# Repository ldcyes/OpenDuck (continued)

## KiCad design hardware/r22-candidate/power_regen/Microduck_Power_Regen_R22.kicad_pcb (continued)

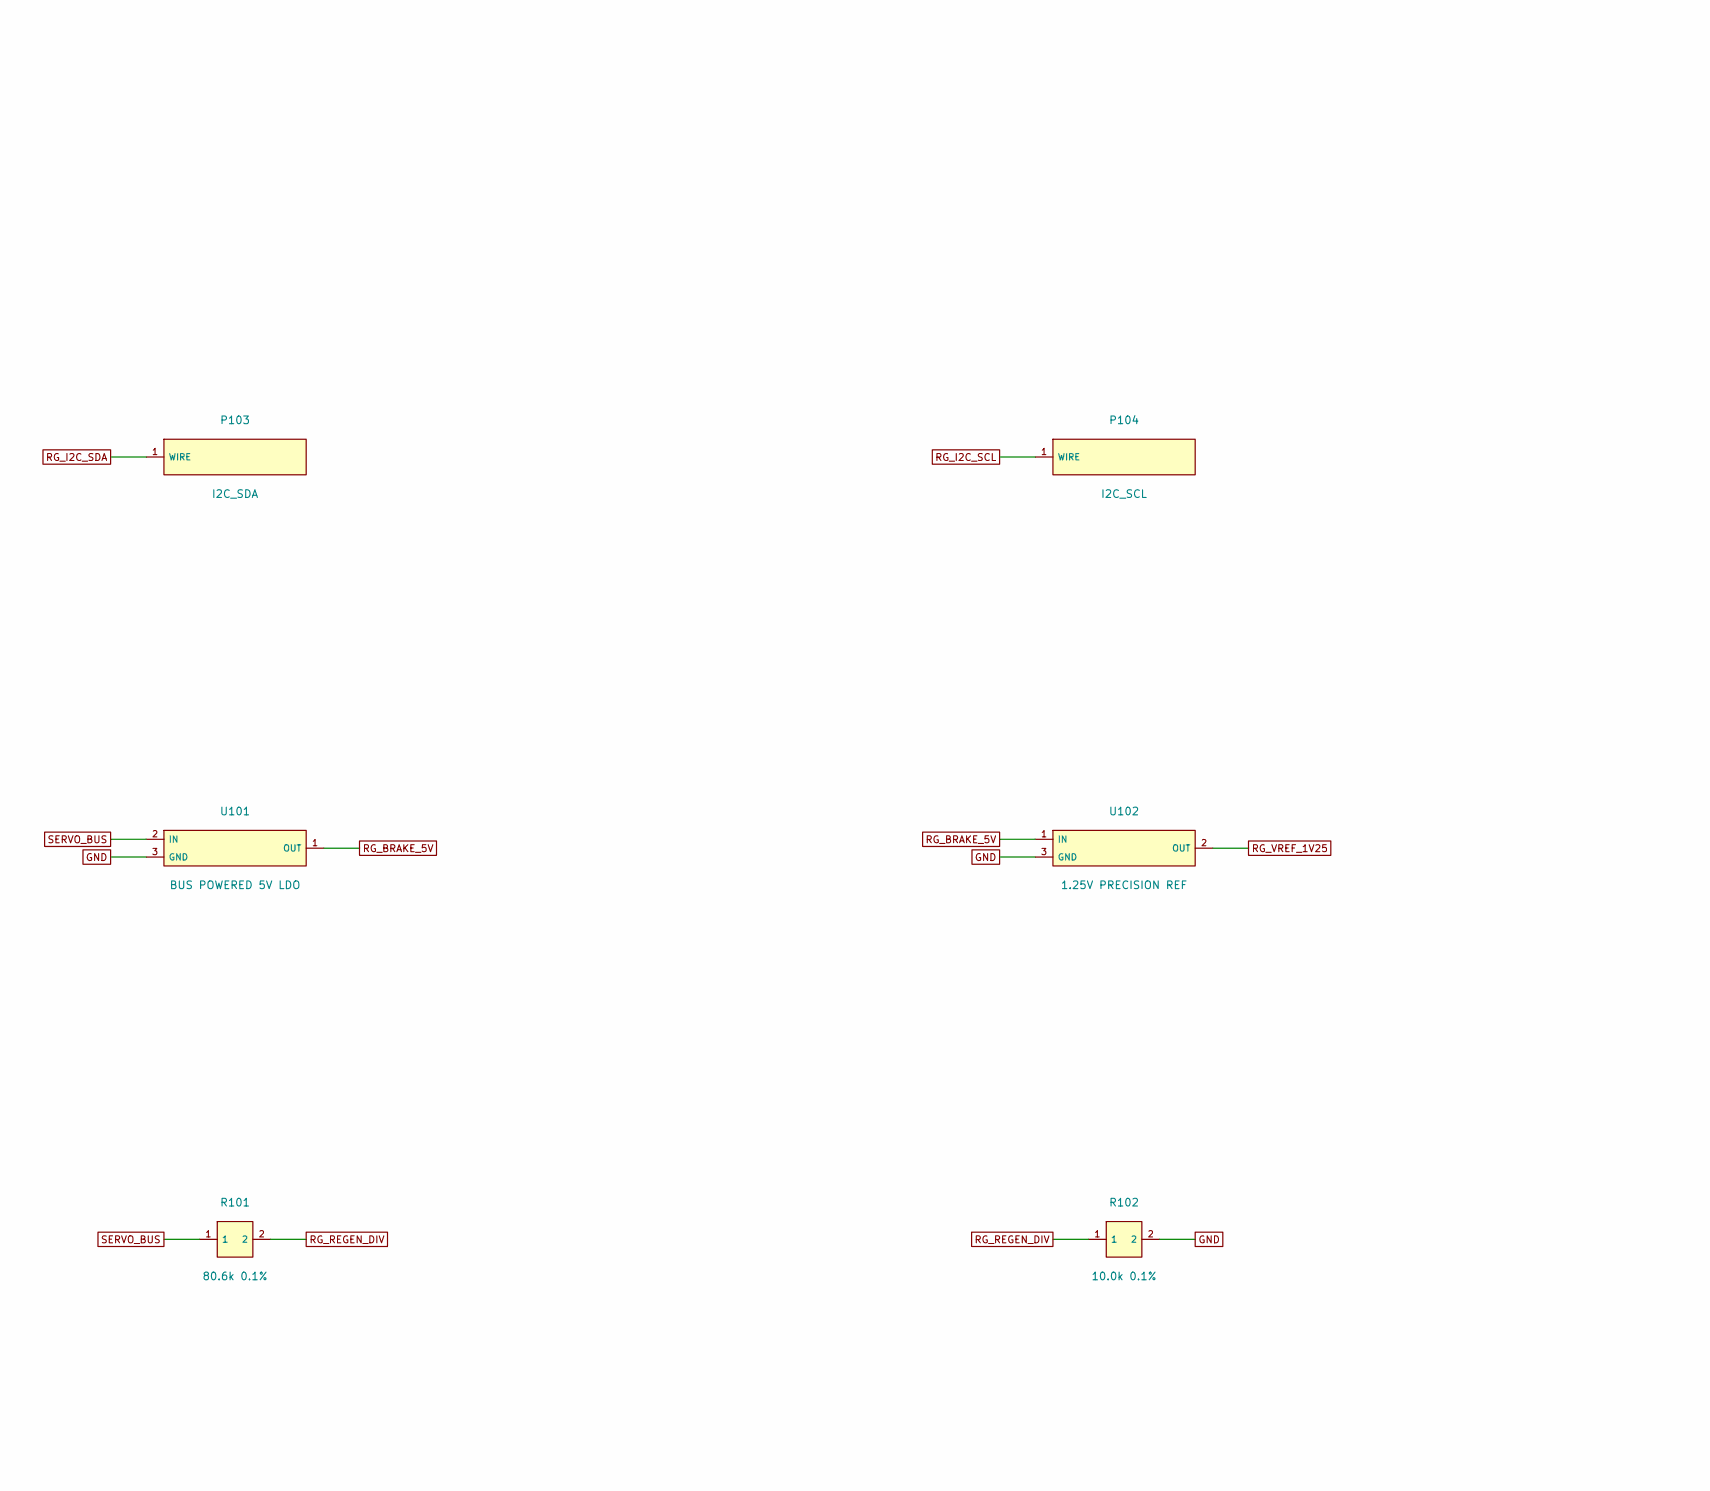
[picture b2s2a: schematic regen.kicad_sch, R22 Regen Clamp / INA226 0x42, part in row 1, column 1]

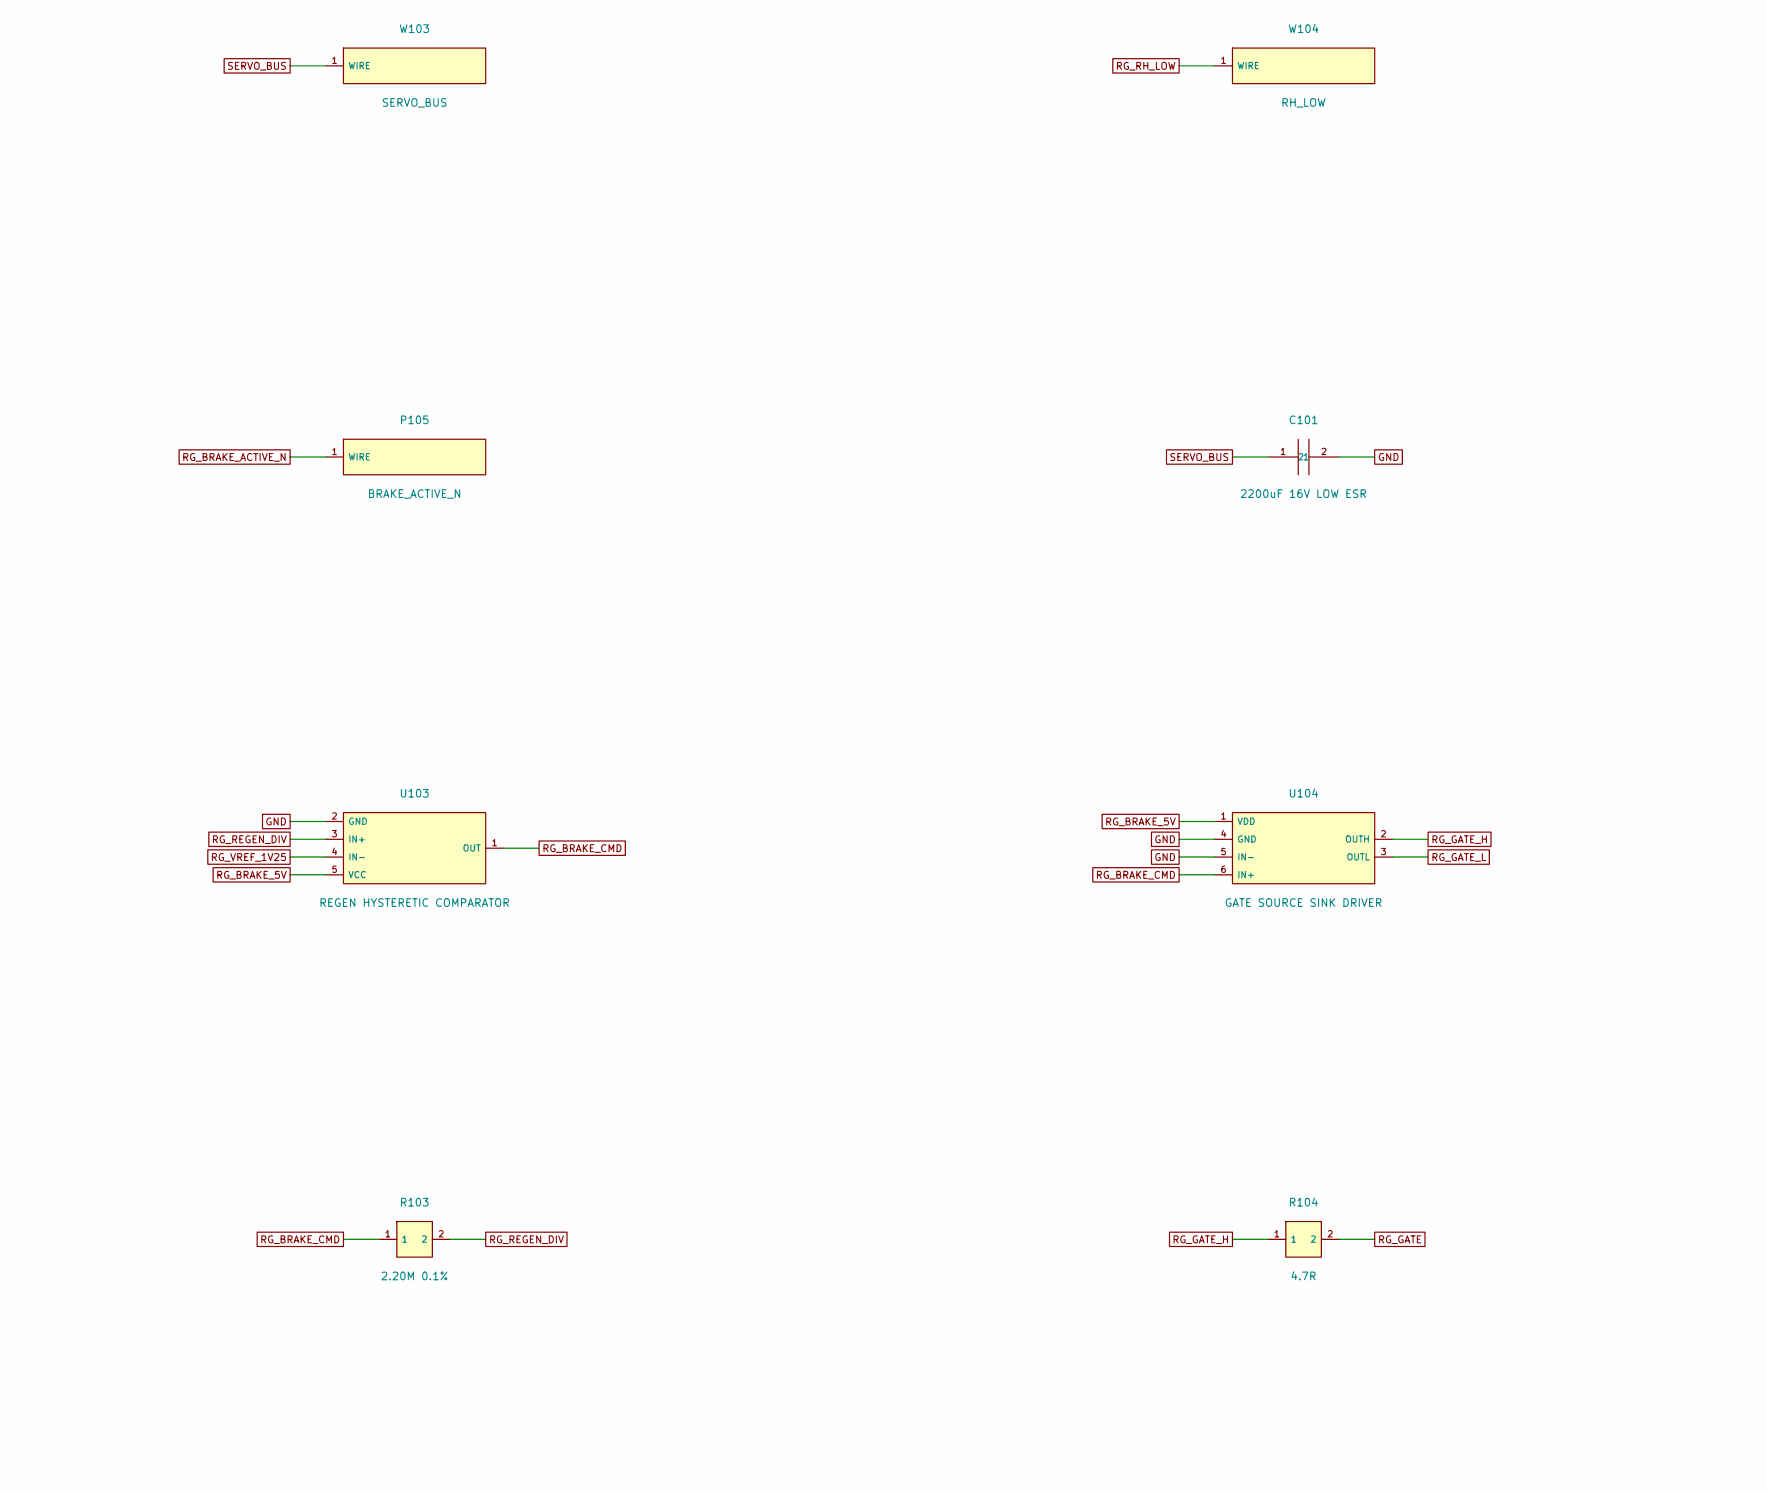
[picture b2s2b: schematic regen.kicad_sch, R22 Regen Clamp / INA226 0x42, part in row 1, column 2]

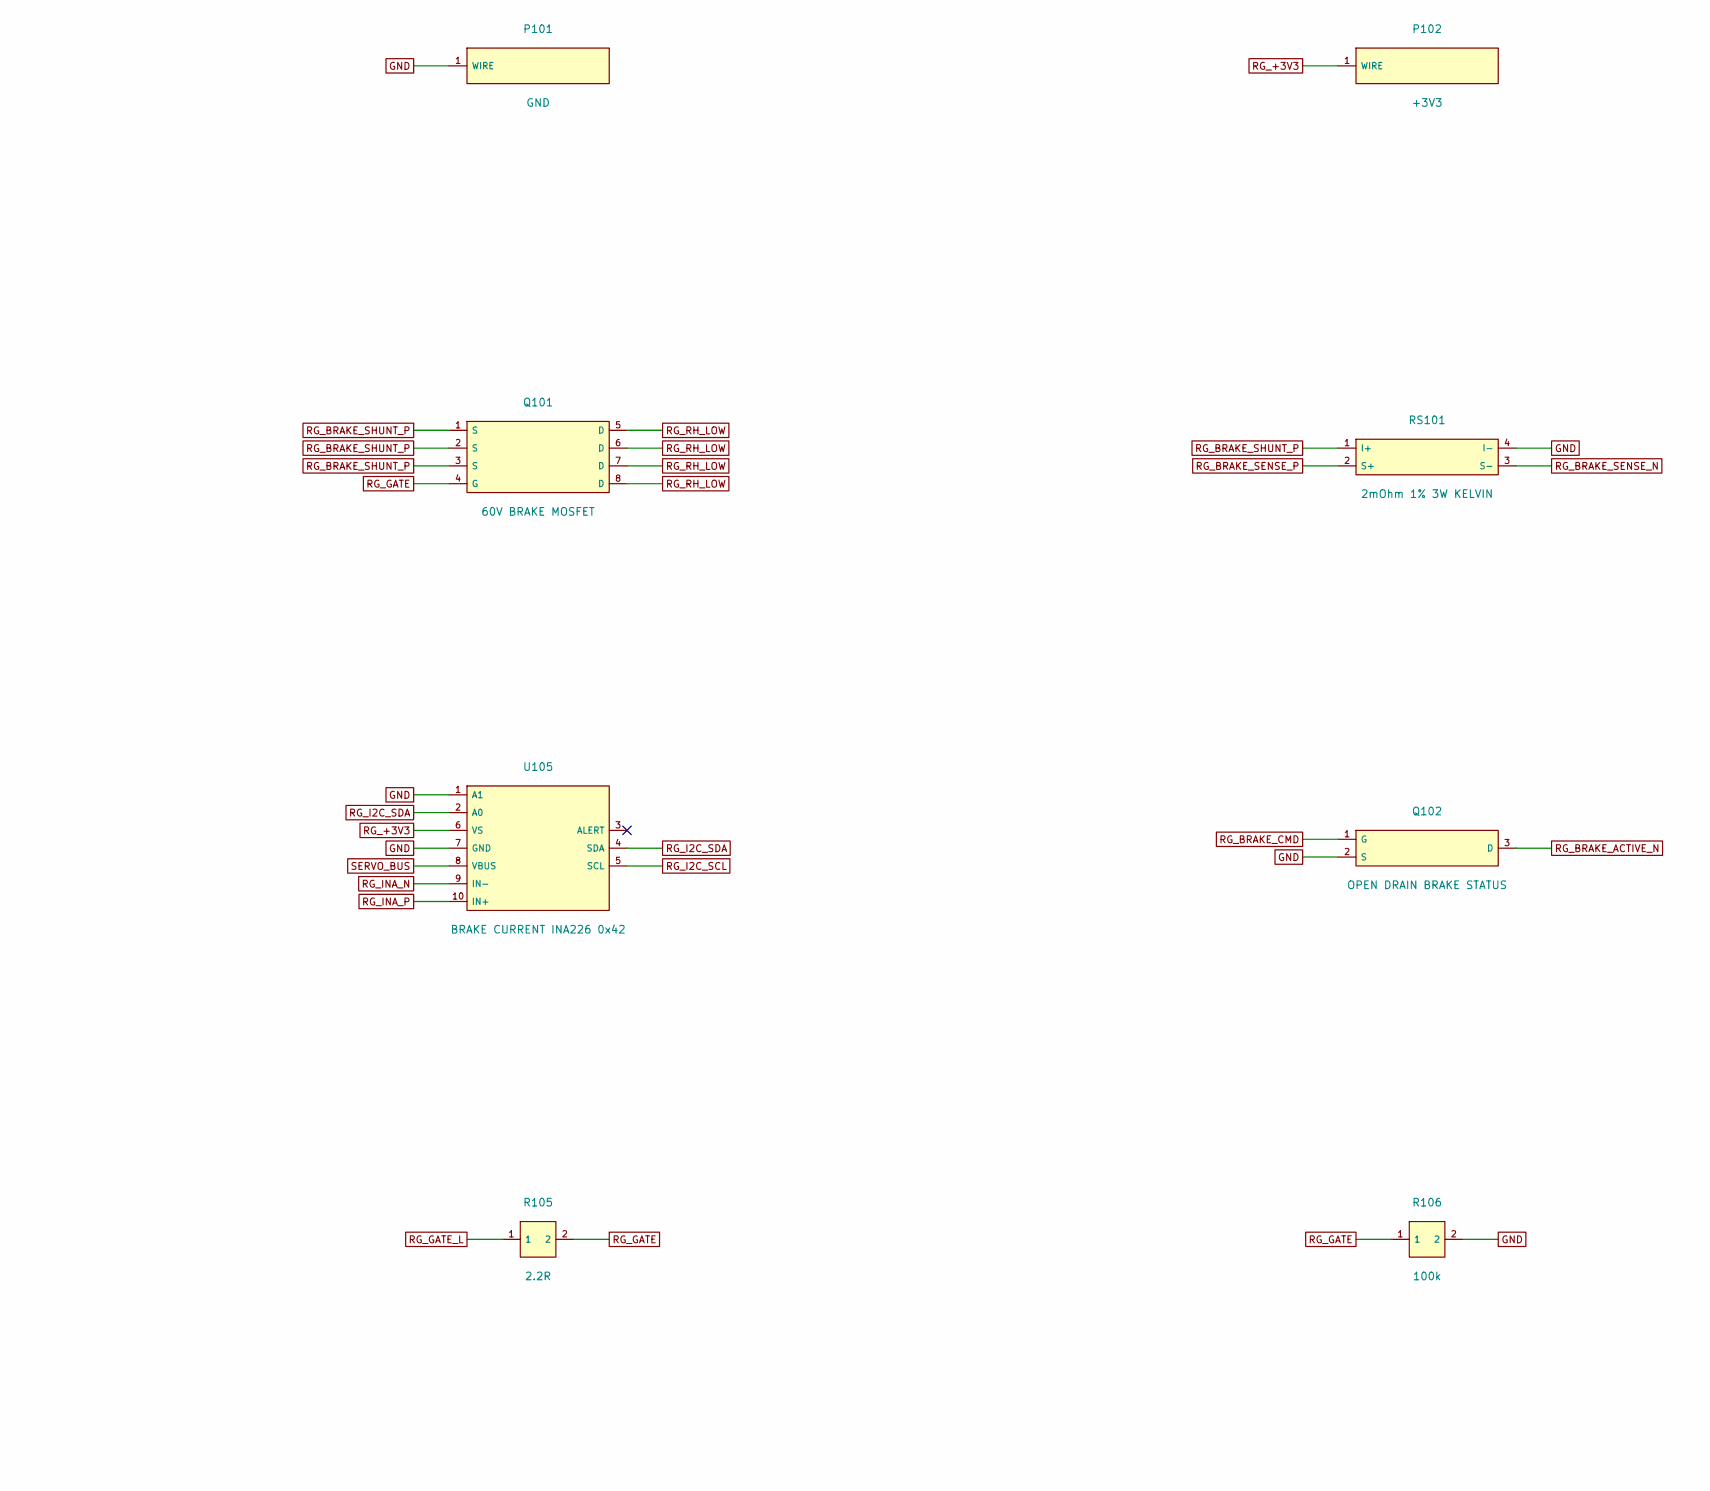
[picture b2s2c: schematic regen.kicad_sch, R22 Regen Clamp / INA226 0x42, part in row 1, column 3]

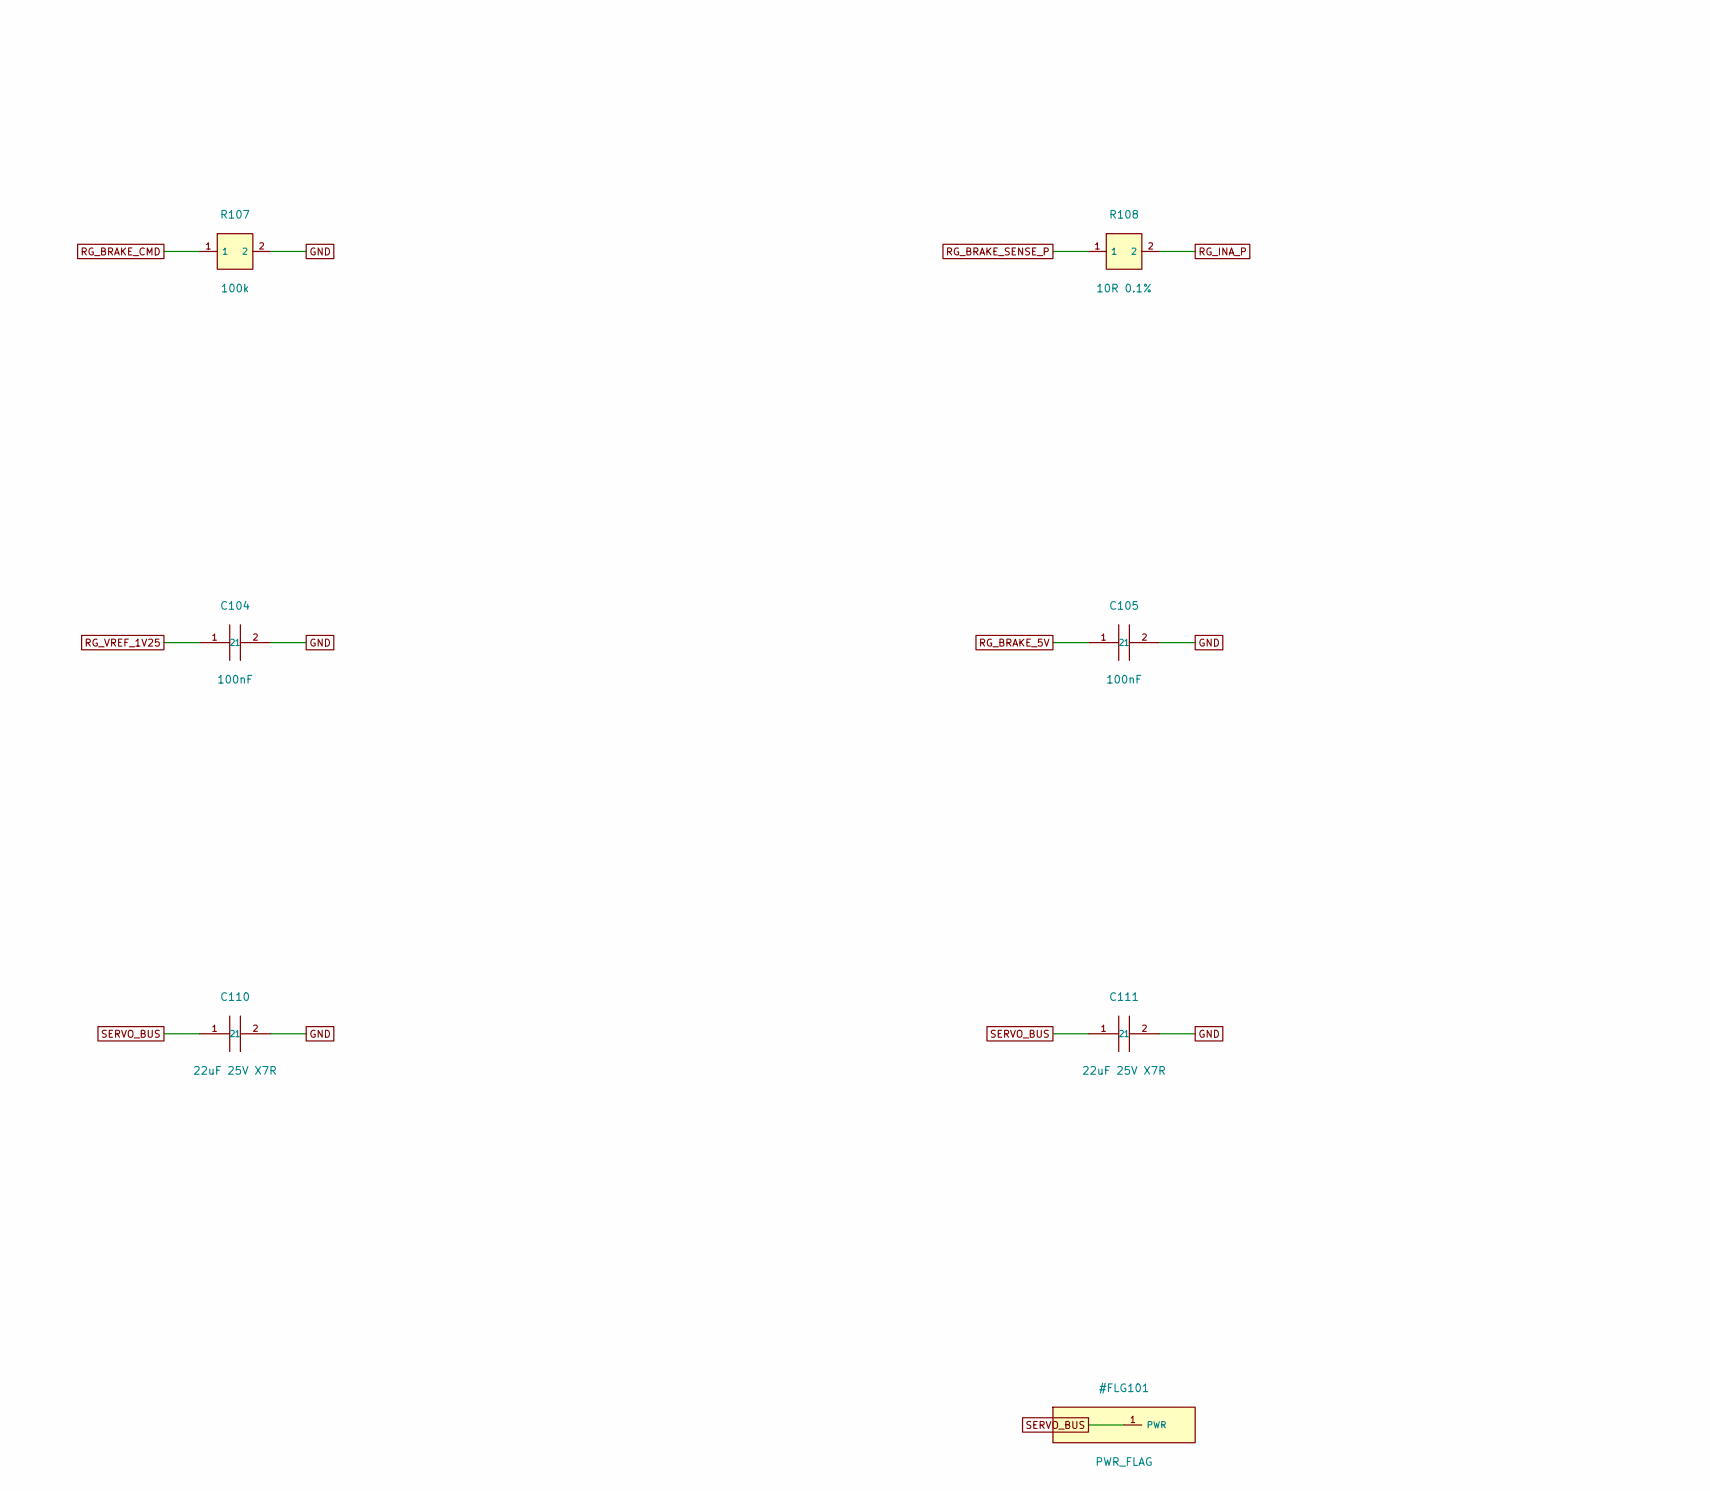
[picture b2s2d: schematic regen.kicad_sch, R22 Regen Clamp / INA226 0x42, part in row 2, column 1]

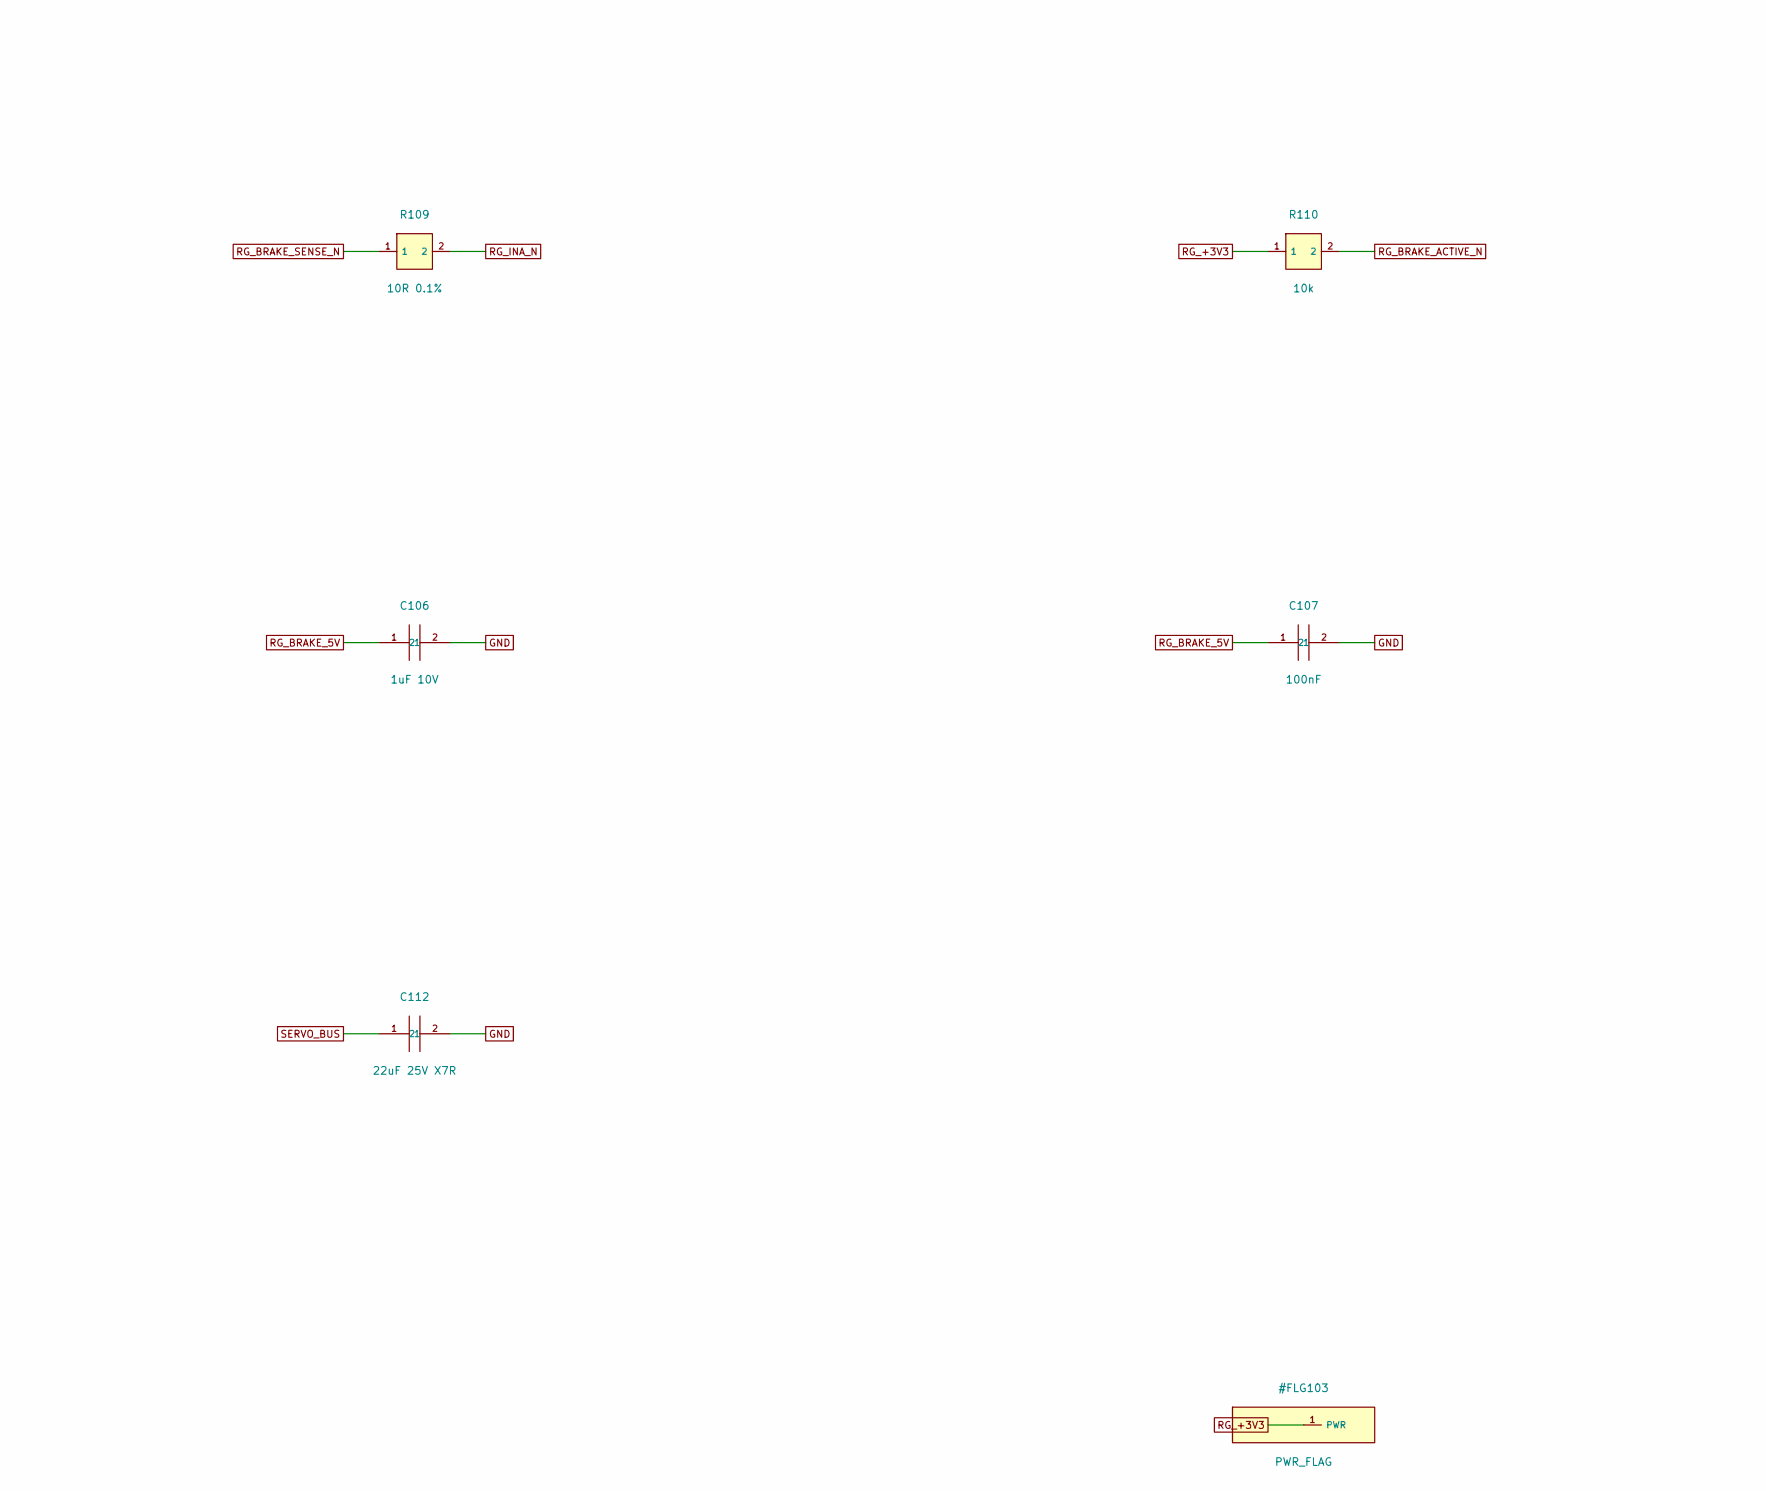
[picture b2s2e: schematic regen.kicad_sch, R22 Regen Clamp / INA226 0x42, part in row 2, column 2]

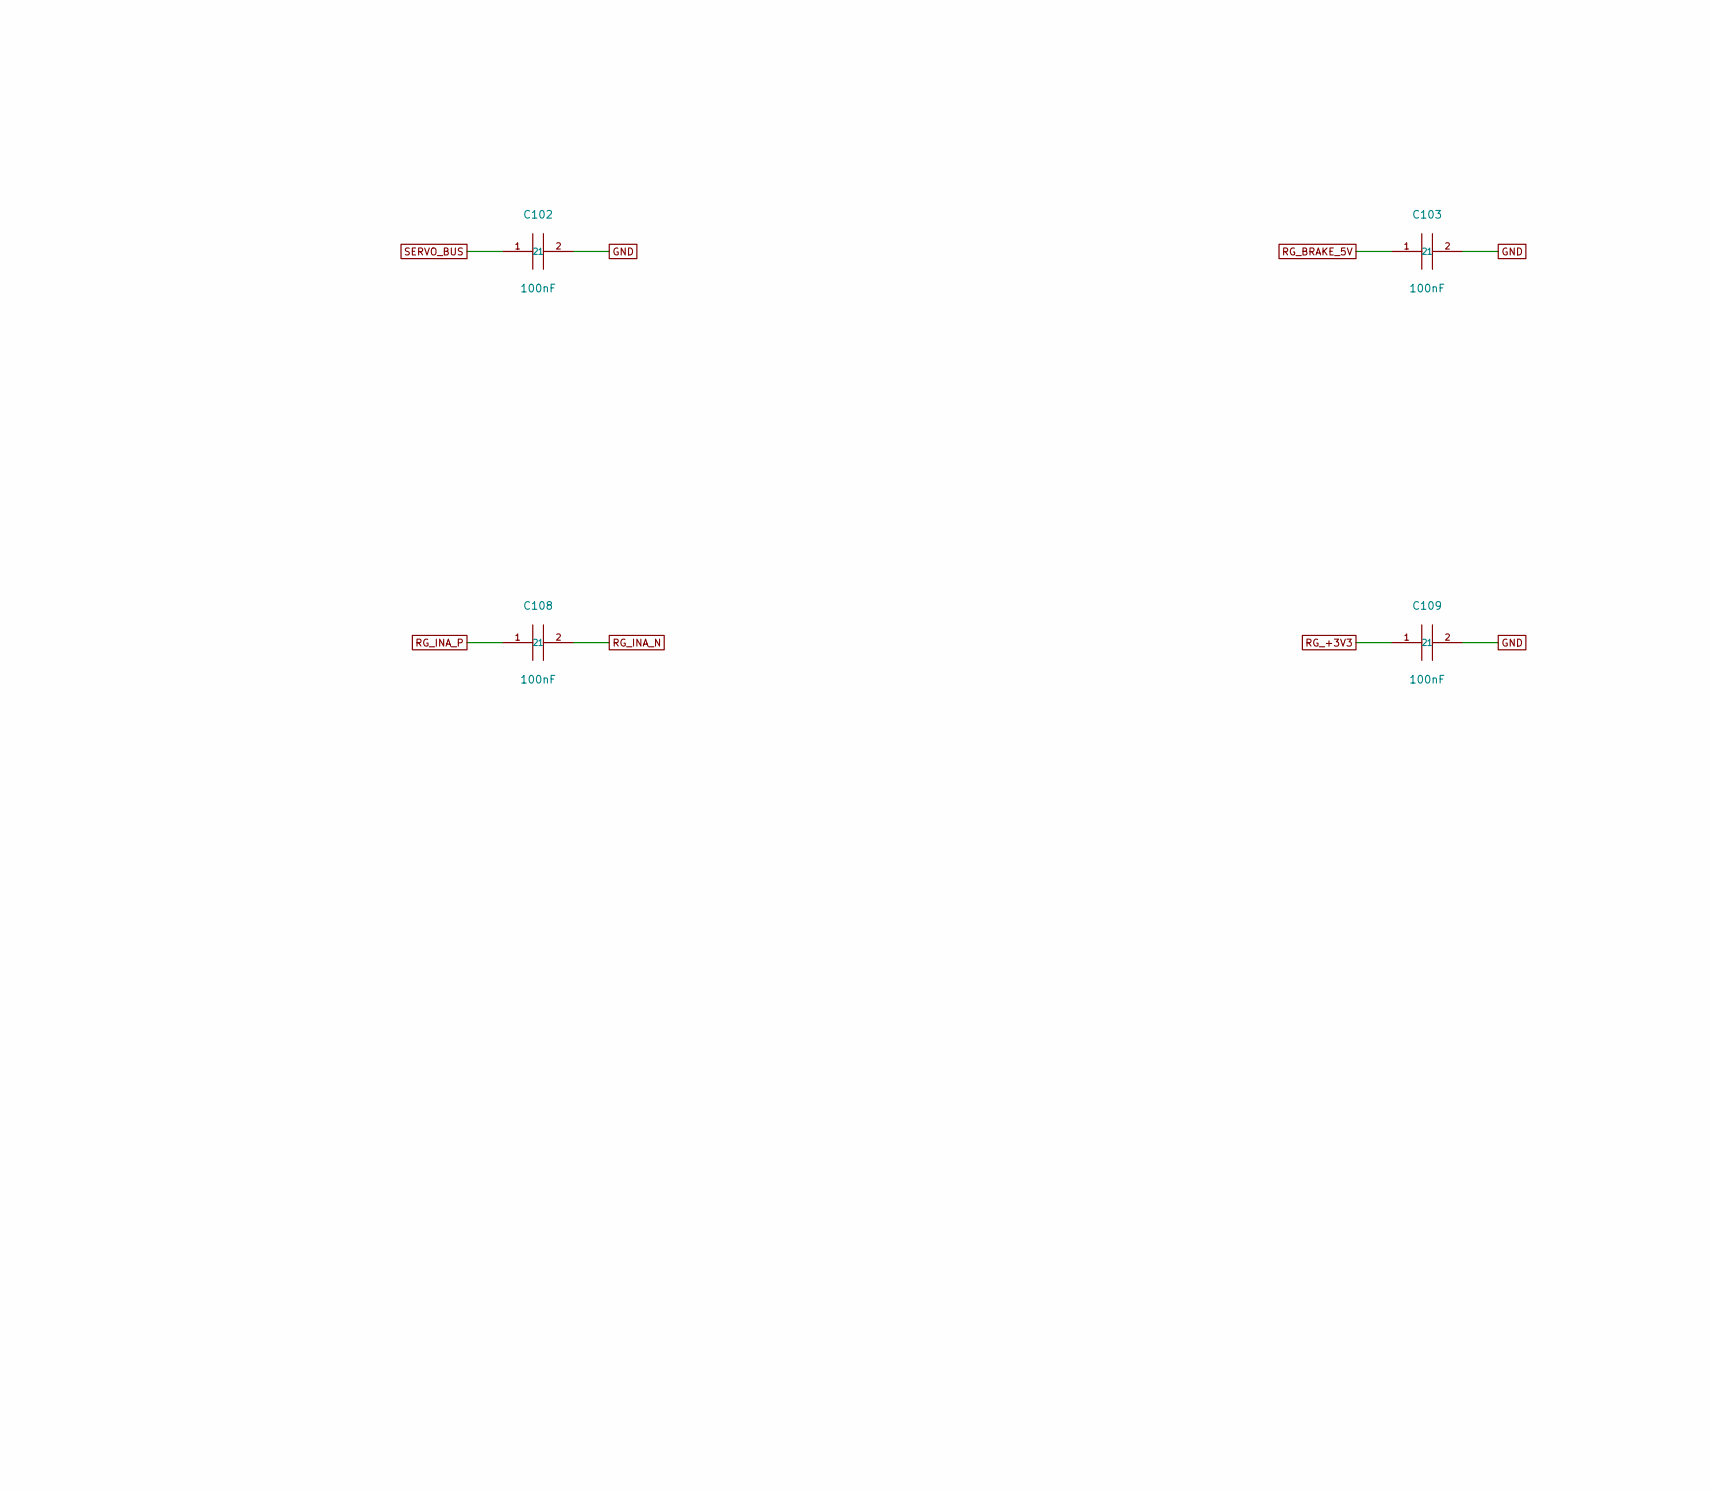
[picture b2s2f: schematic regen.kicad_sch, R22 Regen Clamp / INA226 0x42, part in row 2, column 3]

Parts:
C101: 2200uF 16V LOW ESR; CP_EEUFR1C222_Horizontal_Clip; MPN EEUFR1C222
C102, C103, C104, C105, C107, C108, C109: 100nF; C_0603_1608Metric; MPN GRM188R71H104KA93D
C106: 1uF 10V; C_0603_1608Metric; MPN GRM188R71A105KA61D
C110, C111, C112: 22uF 25V X7R; C_1210_3225Metric; MPN GRM32ER71E226KE15L
P101: GND; WireSignal_0p5mm; MPN SOLDER AWG28 PIGTAIL
P102: +3V3; WireSignal_0p5mm; MPN SOLDER AWG28 PIGTAIL
P103: I2C_SDA; WireSignal_0p5mm; MPN SOLDER AWG28 PIGTAIL
P104: I2C_SCL; WireSignal_0p5mm; MPN SOLDER AWG28 PIGTAIL
P105: BRAKE_ACTIVE_N; WireSignal_0p5mm; MPN SOLDER AWG28 PIGTAIL
Q101: 60V BRAKE MOSFET; CSD18540Q5B_DNK; MPN CSD18540Q5B
Q102: OPEN DRAIN BRAKE STATUS; SOT-23; MPN BSS138
R101: 80.6k 0.1%; R_0603_1608Metric; MPN RT0603BRD0780K6L
R102: 10.0k 0.1%; R_0603_1608Metric; MPN RT0603BRD0710KL
R103: 2.20M 0.1%; R_0603_1608Metric; MPN RT0603BRD072M2L
R104: 4.7R; R_0603_1608Metric; MPN ERJ-3EKF4R7V
R105: 2.2R; R_0603_1608Metric; MPN ERJ-3EKF2R2V
R106, R107: 100k; R_0603_1608Metric; MPN ERJ-3EKF1003V
R108, R109: 10R 0.1%; R_0603_1608Metric; MPN RT0603BRD0710RL
R110: 10k; R_0603_1608Metric; MPN ERJ-3EKF1002V
RS101: 2mOhm 1% 3W KELVIN; WSL2726_Kelvin; MPN WSL27262L000FEA
U101: BUS POWERED 5V LDO; SOT-23; MPN TLV76050DBZR
U102: 1.25V PRECISION REF; SOT-23; MPN REF3312AIDBZR
U103: REGEN HYSTERETIC COMPARATOR; SOT-23-5; MPN TLV3201AIDBVR
U104: GATE SOURCE SINK DRIVER; SOT-23-6; MPN UCC27511DBVR
U105: BRAKE CURRENT INA226 0x42; TI_DGS0010A_1p45x0p30; MPN INA226AIDGSR
W103: SERVO_BUS; WirePad_2p4mm_6mm; MPN SOLDER AWG16
W104: RH_LOW; WirePad_2p4mm_6mm; MPN SOLDER AWG16

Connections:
GND: C101.2, C102.2, C103.2, C104.2, C105.2, C106.2, C107.2, C109.2, C110.2, C111.2, C112.2, P101.1, Q102.2 (S), R102.2, R106.2, R107.2, RS101.4 (I-), U101.3 (GND), U102.3 (GND), U103.2 (GND), U104.4 (GND), U104.5 (IN-), U105.1 (A1), U105.7 (GND); also elsewhere on the board
RG_+3V3: C109.1, P102.1, R110.1, U105.6 (VS)
RG_BRAKE_5V: C103.1, C105.1, C106.1, C107.1, U101.1 (OUT), U102.1 (IN), U103.5 (VCC), U104.1 (VDD)
RG_BRAKE_ACTIVE_N: P105.1, Q102.3 (D), R110.2
RG_BRAKE_CMD: Q102.1 (G), R103.1, R107.1, U103.1 (OUT), U104.6 (IN+)
RG_BRAKE_SENSE_N: R109.1, RS101.3 (S-)
RG_BRAKE_SENSE_P: R108.1, RS101.2 (S+)
RG_BRAKE_SHUNT_P: Q101.1 (S), Q101.2 (S), Q101.3 (S), RS101.1 (I+)
RG_GATE: Q101.4 (G), R104.2, R105.2, R106.1
RG_GATE_H: R104.1, U104.2 (OUTH)
RG_GATE_L: R105.1, U104.3 (OUTL)
RG_I2C_SCL: P104.1, U105.5 (SCL)
RG_I2C_SDA: P103.1, U105.2 (A0), U105.4 (SDA)
RG_INA_N: C108.2, R109.2, U105.9 (IN-)
RG_INA_P: C108.1, R108.2, U105.10 (IN+)
RG_REGEN_DIV: R101.2, R102.1, R103.2, U103.3 (IN+)
RG_RH_LOW: Q101.5 (D), Q101.6 (D), Q101.7 (D), Q101.8 (D), W104.1
RG_VREF_1V25: C104.1, U102.2 (OUT), U103.4 (IN-)
SERVO_BUS: C101.1, C102.1, C110.1, C111.1, C112.1, R101.1, U101.2 (IN), U105.8 (VBUS), W103.1; also elsewhere on the board

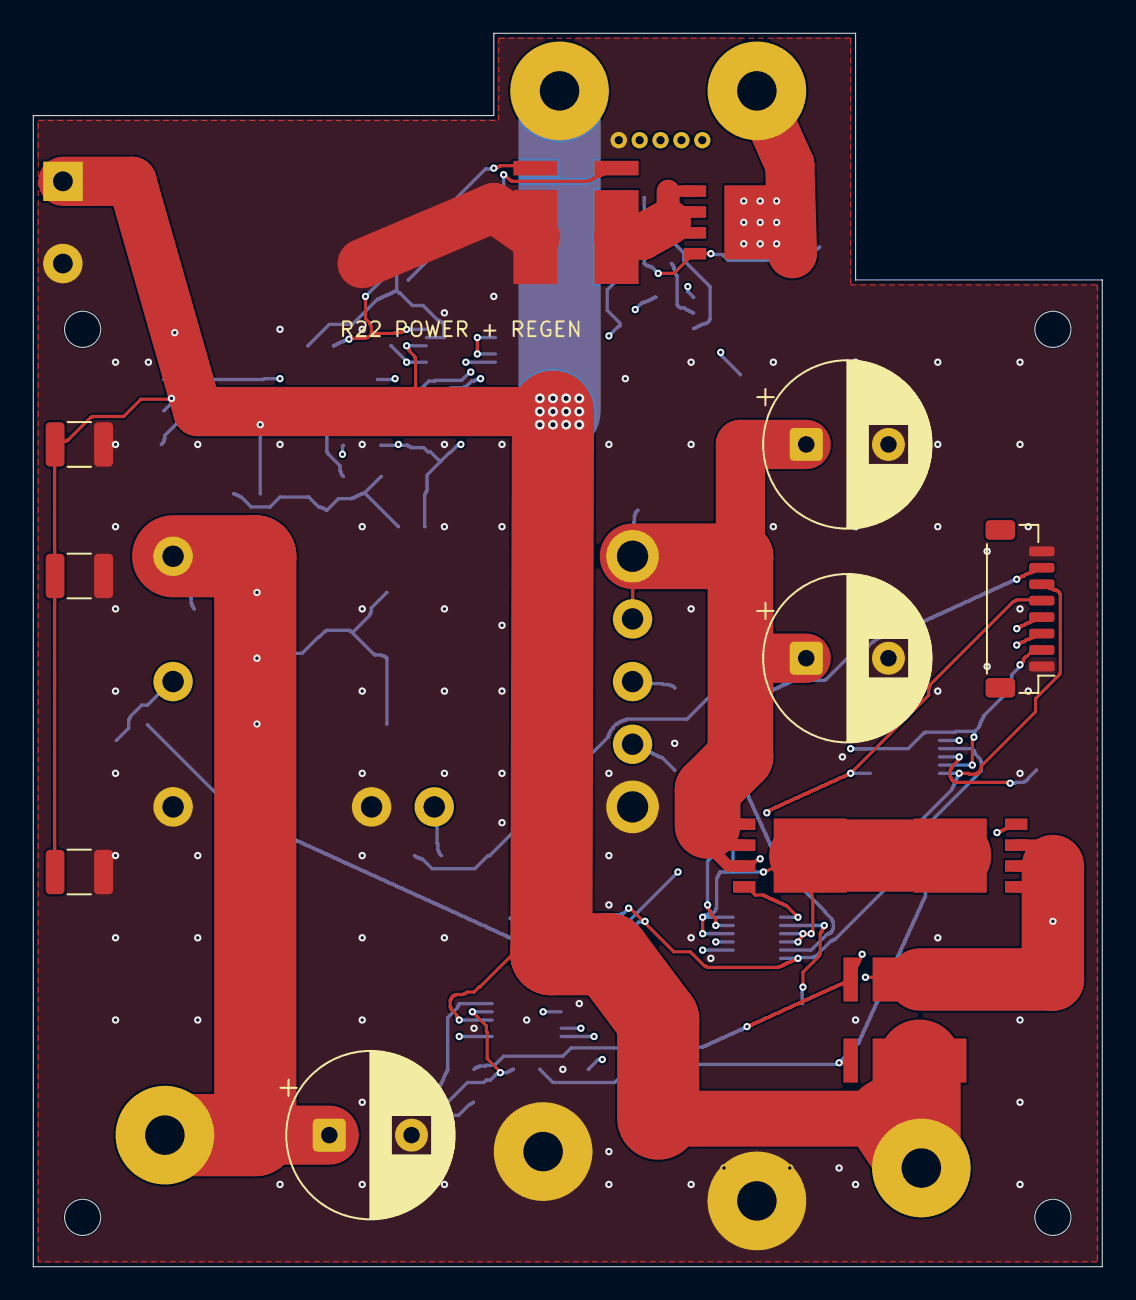
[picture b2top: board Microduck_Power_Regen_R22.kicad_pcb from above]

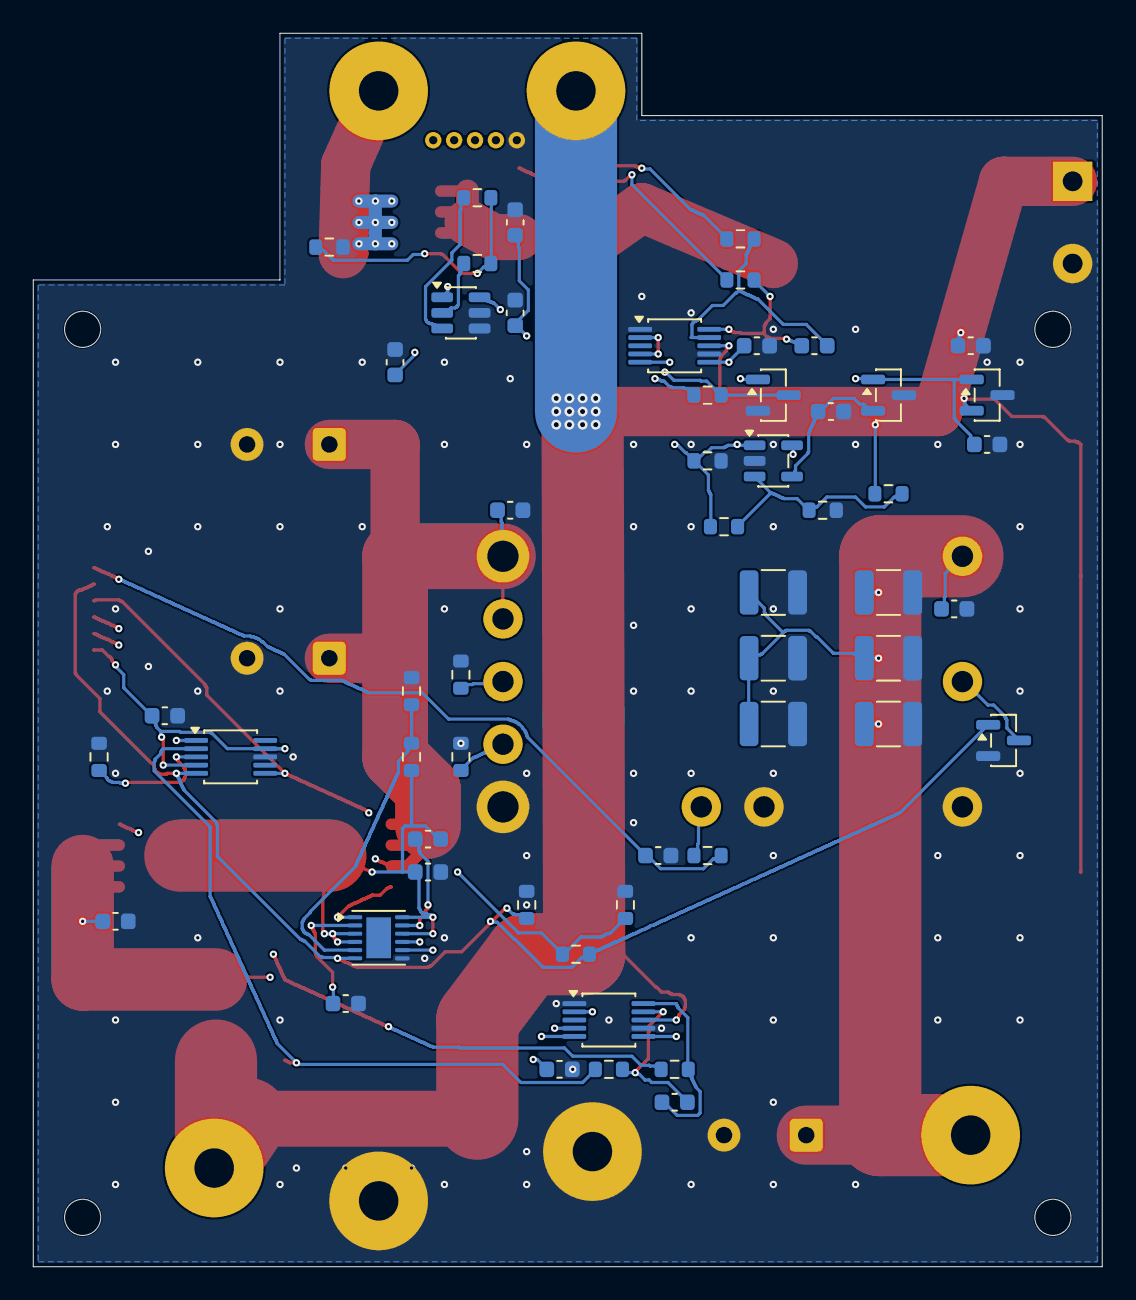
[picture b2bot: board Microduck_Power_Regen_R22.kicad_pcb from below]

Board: 4 copper layers, 65.0 x 75.0 mm, 84 parts (55 on the bottom side), 42 nets.
